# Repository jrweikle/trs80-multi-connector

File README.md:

# trs80-multi-connector

Hopefully allows more than one I/O unit to be attached to a TRS80 Model 3/4.
Boards have been order testing will happen after they arrive.

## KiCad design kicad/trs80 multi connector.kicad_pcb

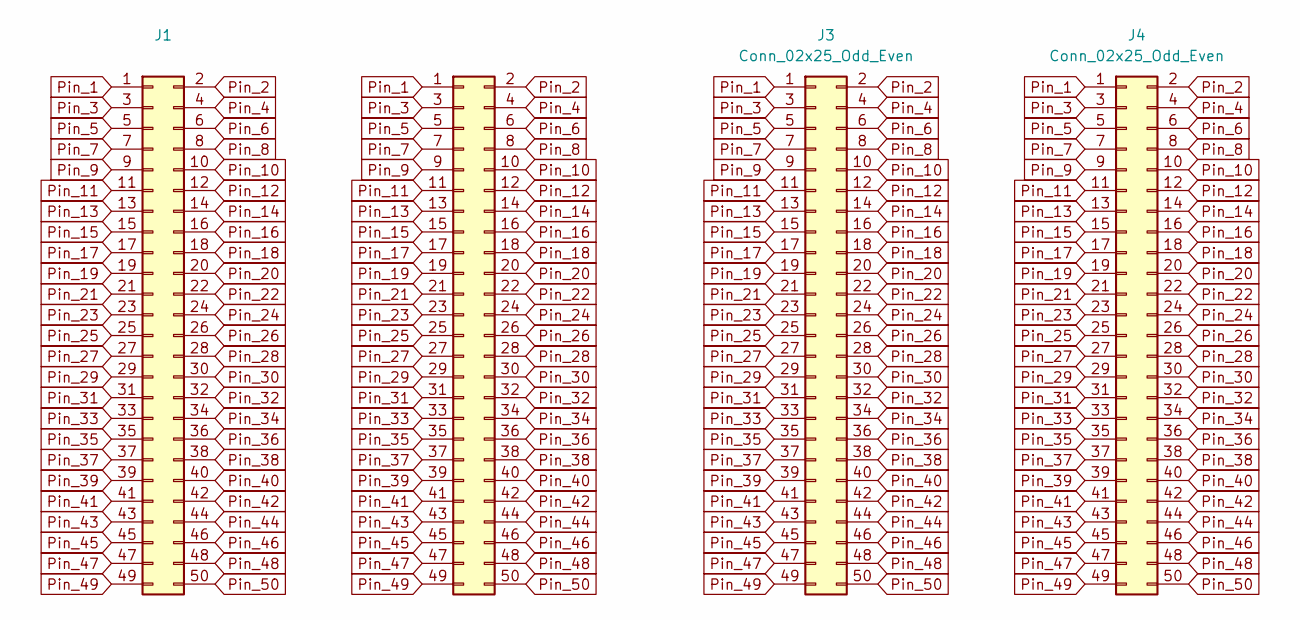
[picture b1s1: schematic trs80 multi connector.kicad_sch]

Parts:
J1, J2, J3, J4: Conn_02x25_Odd_Even; PinHeader_2x25_P2.54mm_Vertical

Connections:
Pin_1: J1.1, J2.1, J3.1, J4.1
Pin_2: J1.2, J2.2, J3.2, J4.2
Pin_3: J1.3, J2.3, J3.3, J4.3
Pin_4: J1.4, J2.4, J3.4, J4.4
Pin_5: J1.5, J2.5, J3.5, J4.5
Pin_6: J1.6, J2.6, J3.6, J4.6
Pin_7: J1.7, J2.7, J3.7, J4.7
Pin_8: J1.8, J2.8, J3.8, J4.8
Pin_9: J1.9, J2.9, J3.9, J4.9
Pin_10: J1.10, J2.10, J3.10, J4.10
Pin_11: J1.11, J2.11, J3.11, J4.11
Pin_12: J1.12, J2.12, J3.12, J4.12
Pin_13: J1.13, J2.13, J3.13, J4.13
Pin_14: J1.14, J2.14, J3.14, J4.14
Pin_15: J1.15, J2.15, J3.15, J4.15
Pin_16: J1.16, J2.16, J3.16, J4.16
Pin_17: J1.17, J2.17, J3.17, J4.17
Pin_18: J1.18, J2.18, J3.18, J4.18
Pin_19: J1.19, J2.19, J3.19, J4.19
Pin_20: J1.20, J2.20, J3.20, J4.20
Pin_21: J1.21, J2.21, J3.21, J4.21
Pin_22: J1.22, J2.22, J3.22, J4.22
Pin_23: J1.23, J2.23, J3.23, J4.23
Pin_24: J1.24, J2.24, J3.24, J4.24
Pin_25: J1.25, J2.25, J3.25, J4.25
Pin_26: J1.26, J2.26, J3.26, J4.26
Pin_27: J1.27, J2.27, J3.27, J4.27
Pin_28: J1.28, J2.28, J3.28, J4.28
Pin_29: J1.29, J2.29, J3.29, J4.29
Pin_30: J1.30, J2.30, J3.30, J4.30
Pin_31: J1.31, J2.31, J3.31, J4.31
Pin_32: J1.32, J2.32, J3.32, J4.32
Pin_33: J1.33, J2.33, J3.33, J4.33
Pin_34: J1.34, J2.34, J3.34, J4.34
Pin_35: J1.35, J2.35, J3.35, J4.35
Pin_36: J1.36, J2.36, J3.36, J4.36
Pin_37: J1.37, J2.37, J3.37, J4.37
Pin_38: J1.38, J2.38, J3.38, J4.38
Pin_39: J1.39, J2.39, J3.39, J4.39
Pin_40: J1.40, J2.40, J3.40, J4.40
Pin_41: J1.41, J2.41, J3.41, J4.41
Pin_42: J1.42, J2.42, J3.42, J4.42
Pin_43: J1.43, J2.43, J3.43, J4.43
Pin_44: J1.44, J2.44, J3.44, J4.44
Pin_45: J1.45, J2.45, J3.45, J4.45
Pin_46: J1.46, J2.46, J3.46, J4.46
Pin_47: J1.47, J2.47, J3.47, J4.47
Pin_48: J1.48, J2.48, J3.48, J4.48
Pin_49: J1.49, J2.49, J3.49, J4.49
Pin_50: J1.50, J2.50, J3.50, J4.50

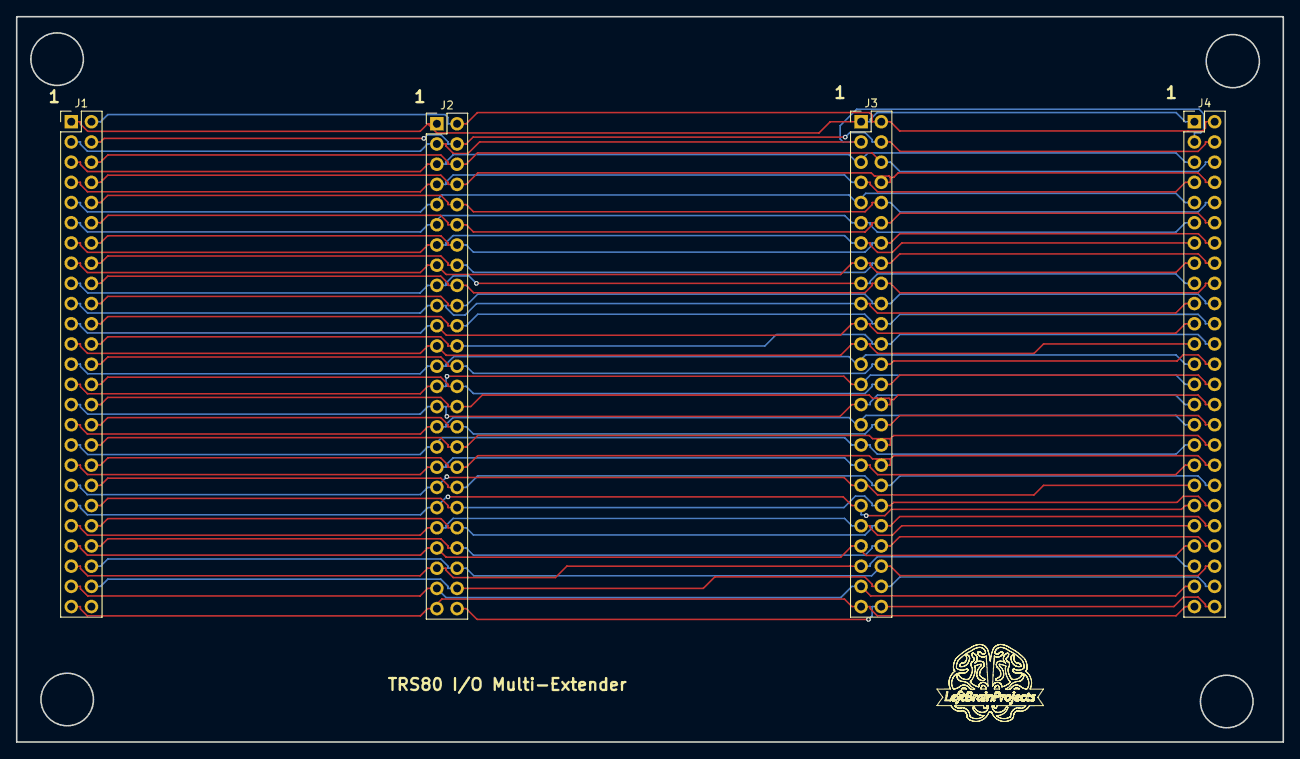
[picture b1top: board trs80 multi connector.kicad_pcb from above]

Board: 2 copper layers, 159.3 x 91.2 mm, 4 parts (0 on the bottom side), 50 nets.

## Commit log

2024-06-17 Create gerbers
2024-06-17 Create kicad
